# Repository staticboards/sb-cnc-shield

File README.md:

# This is the staticboards Arduino CNC shield for low-cost CNC machines.

This is a rework of the original arduino cnc shiled http://blog.protoneer.co.nz/arduino-cnc-shield/

## Why did you make a new Arduino CNC shield?

We were trying to make a new **low-cost** CNC machine for makers and hobbyist.

We found that it is not hard to design a simple aluminum structure with some 3d printed parts, using open software like FreeCAD.

But surprising, there are not many options for electronics part. And we didn’t find any open source shield for Arduino. Maybe we are wrong! But with a quick search, we didn't find anything.

We found one **Arduino CNC** shield that is being sold on eBay or Aliexpress. But the authors don’t like the idea of Chinese manufacturers making boards without any real collaboration (*something that I agree, open hardware is about community*). I couldnt find source files for this board.

So, as we decided that it is time to learn KiCad (a real open source software for PCB design), and we decided to make the PCB of this board, using the same pin layout, to get experience with KiCad.

And this is the final result: The **SB CNC Shield for Arduino Uno, 100% compatible with GRBL**.

We followed the same philosophy of our popular RAMPS 1.4 SB: Branded components, like the Molex connector, beautiful design with the black PCB and golden finish, and fully tested before shipping.

## What can you do with the SB CNC Shield?

The main idea behind this shield is that you can make your own functional CNC with a limited budget.

If you are interested in robots, you should make your own CNC machine. There are many problems that are not obvious at first. Motors, drivers, heat, software, belts, backslash.

Even if you want to buy an expensive machine, and you don't have any previous experience with CNC, it is a very good idea to make one by yourself.

**SB CNC SHIELD is 100% open hardware**. It is designed with *KiCad*, and you can read the schematics, check the PCB design, learn about electronics, improve it, whatever.

And the most important part with Open Hardware, we can create a community, share experiences, new ideas and fix problems.

This board is 100% compatible with the popular GRBL firmware. You don't need special configurations. Plug and Play. 

And there is a huge community behind this project, You can be part of it!

## Why no a full CNC board?

Well, you can go with a complete board. If you are serious about CNC, you should do it. A complete board is autonomous. You don't need a computer to send commands to the machine.

There are some boards open source, with a good community. That is very important if you want good support.
But most of them, they are closed source. Or they have a custom firmware.

For example, some integrated boards include the drivers within the board. That could be a problem. Drivers can get hot and it is not difficult to burn one. And in some cases, it is a good idea to use different drivers for each axis. 

And they have a higher price. Usually more than $100. If you are making a small CNC, for casual projects, this is a big deal.

## What else do I need?

To build a complete CNC machine you will need:

- One Arduino Uno
- At least, 3 drivers for the motors (you can use the popular A4988, or the more powerful DRV8825)
- One bipolar stepper motor for each axis
- One power supply. You can reuse your PC power supply with our ATX Board.
- The spindle (you can use a Dremel or buy a spindle on eBay) or a laser diode.
- The structure (aluminum t-slots, printed parts, etc)

## SB CNC Shield Features

- Beautiful design in Black. With Gold finish,  colored pin headers and a blue reset button.
- Cute easy yellow jumpers!
- 100% Compatible with the GRBL firmware. Plug and Play.
- You can duplicate any axis, or sacrifice your spindle control for a 4th axis. Simply change the jumpers, and duplicate any axis.
- Molex power connector rated at 15A. Cheap Chinese plastic connectors can get burned.
- You can use AWG22 cables for the power supply.
- 35V Capacitors. You can use 24V power supplies without any problem.-
- Endstops for X,Y,Z. You can connect the maximum and minimum limit for each axis.
- Easy to Access Reset button
- Configurable Emergency Button (normally open or normally closed)
- You can use the PWM features in GRBL to control the spindle speed. This is a great feature for metal and wood works.
- You can configure micro stepping for each driver, for a fluid movement.
- External driver connector. You can use professional and expensive drivers, like the Gecko drivers.
- You can use the extended pins from GRBL, like Coolant, Pause/Hold, Resume, and Abort
- UART connectors. You can use a Bluetooth adapter for a wireless CNC machine.
- i2c connection. You can use a temperature sensor for example (but you have to modify the GRBL source code)

## Useful Links

- http://blog.protoneer.co.nz/arduino-cnc-shield/ Original design. It has many guides and tutorials.
- https://github.com/grbl/grbl : GRBL firmware. You should learn how to use it
- https://github.com/winder/Universal-G-Code-Sender Graphical Interface, written in Java
- https://www.staticboards.com/ : Our website
- https://github.com/staticboards/sb-cnc-shield : github original repository

## License

**Creative-Commons 3.0 CC BY-SA**

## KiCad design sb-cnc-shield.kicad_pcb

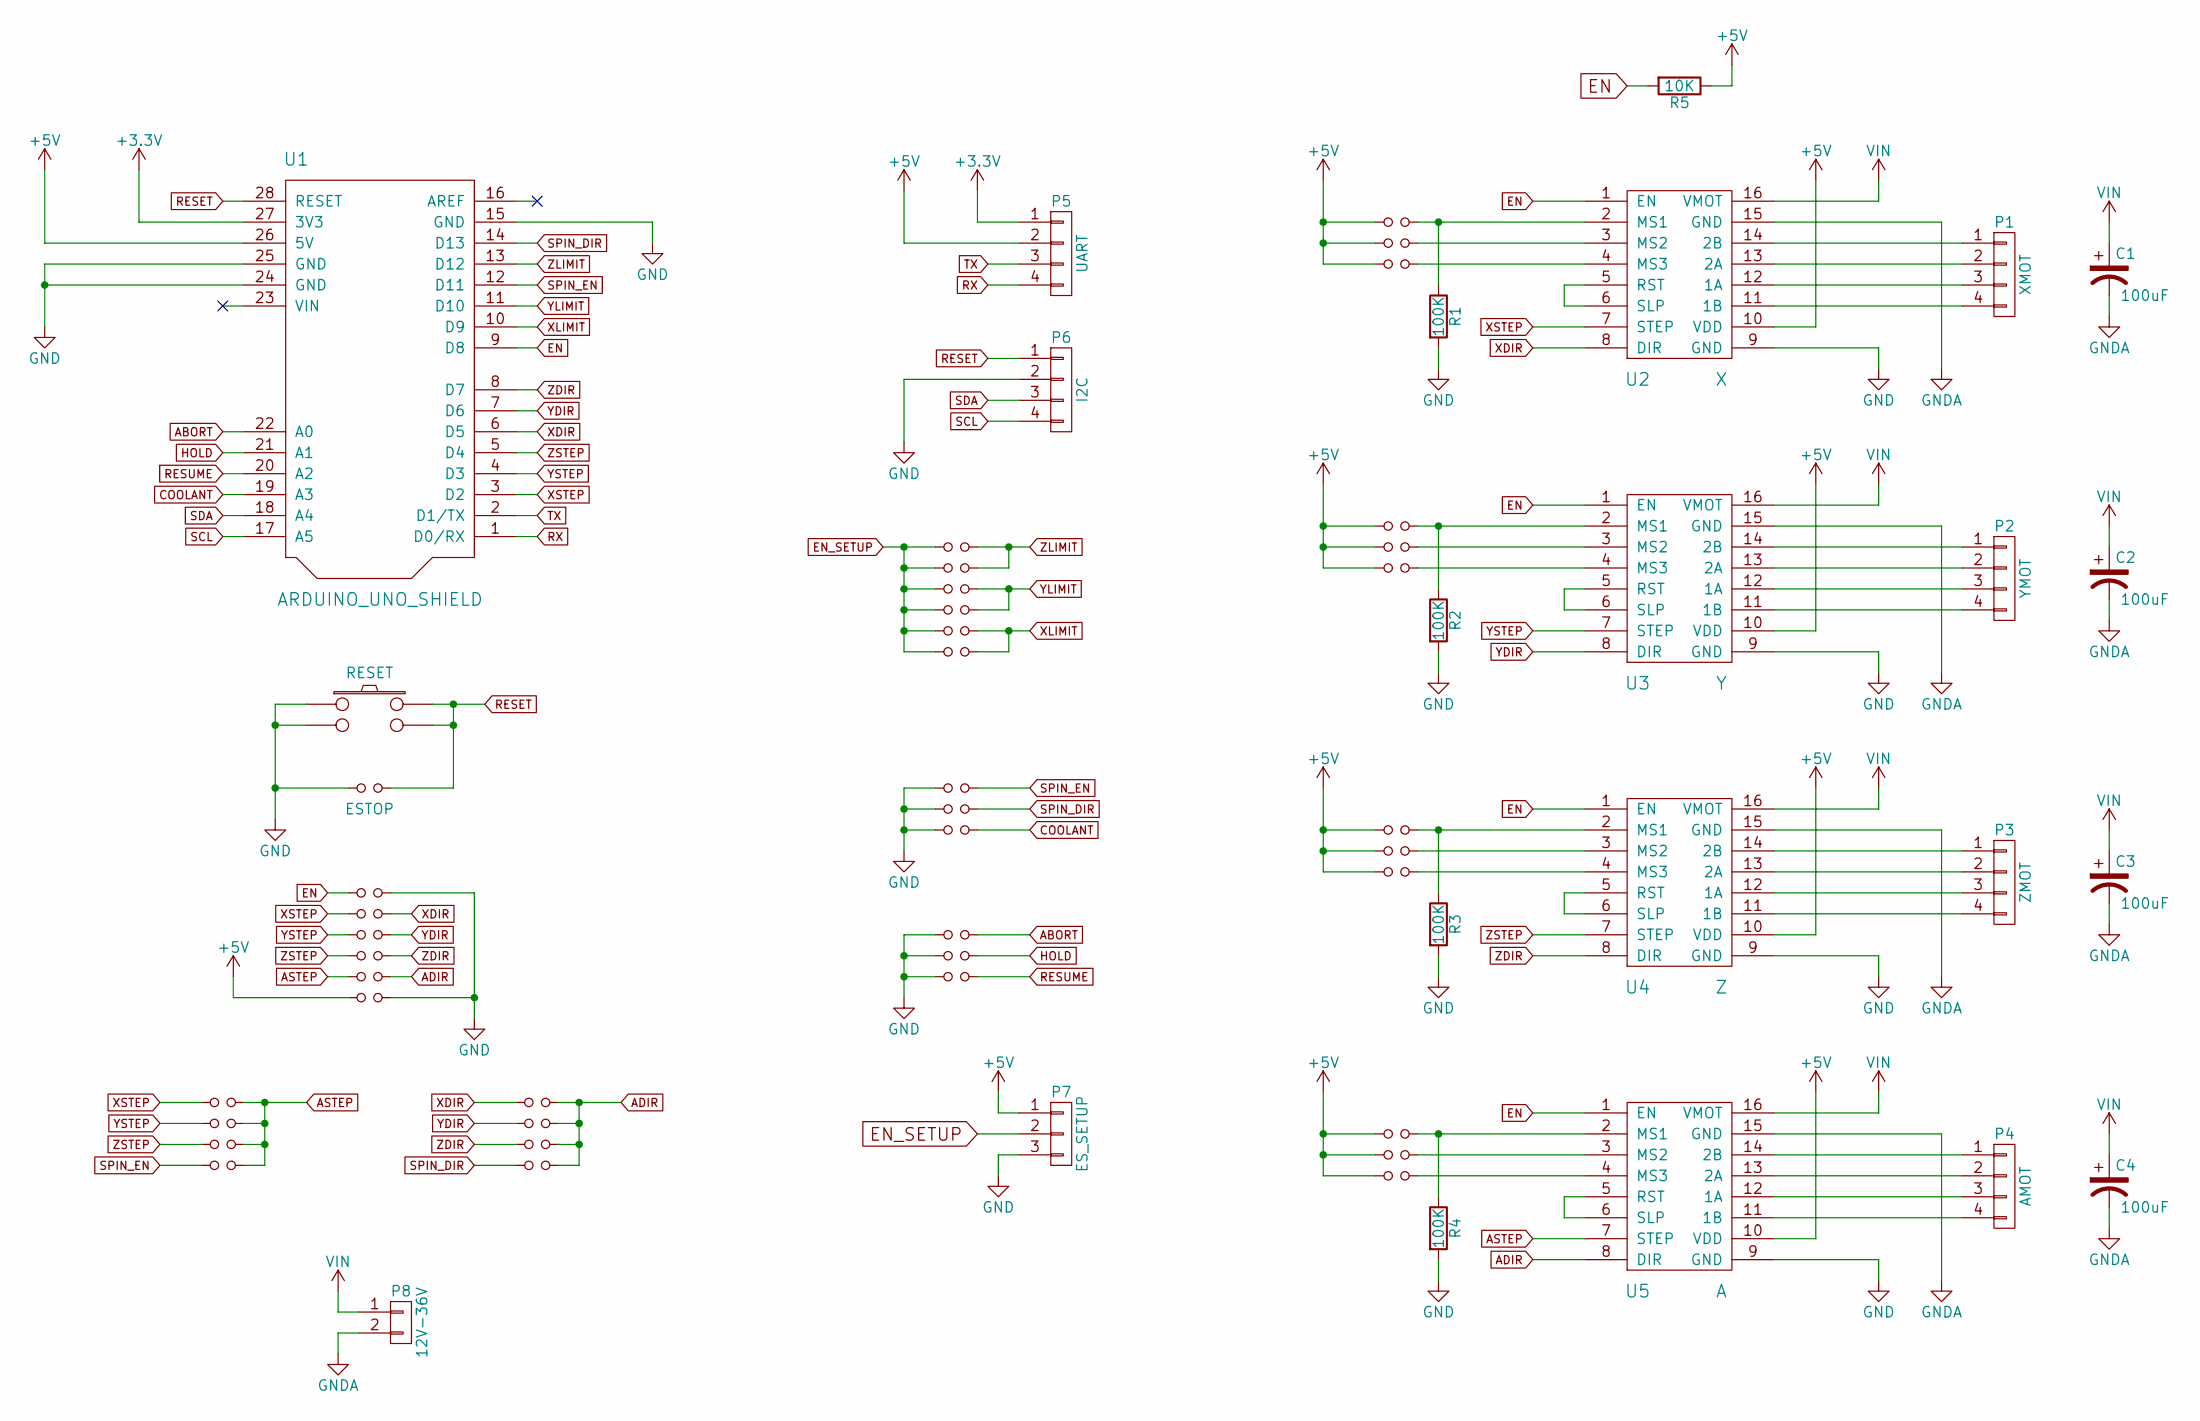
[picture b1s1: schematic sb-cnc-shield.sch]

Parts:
C1, C2, C3, C4: 100uF; c_elec_6.3x7.7
JP1, JP2, JP3, JP4, JP5, JP6, JP7, JP8, JP9, JP10, JP11, JP12, JP32, JP33, JP34, JP35, JP36, JP37, JP38, JP39: Jumper_NO_Small; Pin_100mil_Header_Straight_1x02
JP13: Z+; Pin_100mil_Header_Straight_1x02
JP14: Z-; Pin_100mil_Header_Straight_1x02
JP15: Y+; Pin_100mil_Header_Straight_1x02
JP16: Y-; Pin_100mil_Header_Straight_1x02
JP17: X+; Pin_100mil_Header_Straight_1x02
JP18: X-; Pin_100mil_Header_Straight_1x02
JP19: SpinEn; Pin_100mil_Header_Straight_1x02
JP20: SpinDir; Pin_100mil_Header_Straight_1x02
JP21: CoolEn; Pin_100mil_Header_Straight_1x02
JP22: Abort; Pin_100mil_Header_Straight_1x02
JP23: Hold; Pin_100mil_Header_Straight_1x02
JP24: Resume; Pin_100mil_Header_Straight_1x02
JP25: ESTOP; Pin_100mil_Header_Straight_1x02
JP26: EN/GND; Pin_100mil_Header_Straight_1x02
JP27: XSTEP/DIR; Pin_100mil_Header_Straight_1x02
JP28: YSTEP/DIR; Pin_100mil_Header_Straight_1x02
JP29: ZSTEP/DIR; Pin_100mil_Header_Straight_1x02
JP30: ASTEP/DIR; Pin_100mil_Header_Straight_1x02
JP31: +5V/GND; Pin_100mil_Header_Straight_1x02
P1: XMOT; Pin_Header_Straight_2x04
P2: YMOT; Pin_Header_Straight_2x04
P3: ZMOT; Pin_Header_Straight_2x04
P4: AMOT; Pin_Header_Straight_2x04
P5: UART; Pin_Header_Straight_1x04
P6: I2C; Pin_Header_Straight_1x04
P7: ES_SETUP; Pin_Header_Straight_1x03
P8: 12V-36V; CONN_01x02_PITCH_5.08mm
R1, R2, R3, R4: 100K; R_0805
R5: 10K; R_0805
SW1: RESET; SWITCH_TACTILE_6.5_PTH
U1: ARDUINO_UNO_SHIELD; ARDUINO_SHIELD
U2: X; POLOLU_STEPPER_DRIVER
U3: Y; POLOLU_STEPPER_DRIVER
U4: Z; POLOLU_STEPPER_DRIVER
U5: A; POLOLU_STEPPER_DRIVER

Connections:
+3V3: P5.1, U1.27 (3V3)
+5V: JP1.1, JP2.1, JP3.1, JP4.1, JP5.1, JP6.1, JP7.1, JP8.1, JP9.1, JP10.1, JP11.1, JP12.1, JP31.1, P5.2, P7.1, R5.1, U1.26 (5V), U2.10 (VDD), U3.10 (VDD), U4.10 (VDD), U5.10 (VDD)
ABORT: JP22.2, U1.22 (A0)
ADIR: JP30.2, JP36.2, JP37.2, JP38.2, JP39.2, U5.8 (DIR)
ASTEP: JP30.1, JP32.2, JP33.2, JP34.2, JP35.2, U5.7 (STEP)
COOLANT: JP21.2, U1.19 (A3)
EN: JP26.1, R5.2, U1.9 (D8), U2.1 (EN), U3.1 (EN), U4.1 (EN), U5.1 (EN)
EN_SETUP: JP13.1, JP14.1, JP15.1, JP16.1, JP17.1, JP18.1, P7.2
GND: JP19.1, JP20.1, JP21.1, JP22.1, JP23.1, JP24.1, JP25.1, JP26.2, JP31.2, P6.2, P7.3, R1.2, R2.2, R3.2, R4.2, SW1.1, SW1.2, U1.15 (GND), U1.24 (GND), U1.25 (GND), U2.9 (GND), U3.9 (GND), U4.9 (GND), U5.9 (GND)
GNDA: C1.2, C2.2, C3.2, C4.2, P8.2, U2.15 (GND), U3.15 (GND), U4.15 (GND), U5.15 (GND)
HOLD: JP23.2, U1.21 (A1)
unnamed: JP1.2, R1.1, U2.2 (MS1)
unnamed: JP2.2, U2.3 (MS2)
unnamed: JP3.2, U2.4 (MS3)
unnamed: JP4.2, R2.1, U3.2 (MS1)
unnamed: JP5.2, U3.3 (MS2)
unnamed: JP6.2, U3.4 (MS3)
unnamed: JP7.2, R3.1, U4.2 (MS1)
unnamed: JP8.2, U4.3 (MS2)
unnamed: JP9.2, U4.4 (MS3)
unnamed: JP10.2, R4.1, U5.2 (MS1)
unnamed: JP11.2, U5.3 (MS2)
unnamed: JP12.2, U5.4 (MS3)
unnamed: P1.1, U2.14 (2B)
unnamed: P1.2, U2.13 (2A)
unnamed: P1.3, U2.12 (1A)
unnamed: P1.4, U2.11 (1B)
unnamed: P2.1, U3.14 (2B)
unnamed: P2.2, U3.13 (2A)
unnamed: P2.3, U3.12 (1A)
unnamed: P2.4, U3.11 (1B)
unnamed: P3.1, U4.14 (2B)
unnamed: P3.2, U4.13 (2A)
unnamed: P3.3, U4.12 (1A)
unnamed: P3.4, U4.11 (1B)
unnamed: P4.1, U5.14 (2B)
unnamed: P4.2, U5.13 (2A)
unnamed: P4.3, U5.12 (1A)
unnamed: P4.4, U5.11 (1B)
unnamed: U2.5 (RST), U2.6 (SLP)
unnamed: U3.5 (RST), U3.6 (SLP)
unnamed: U4.5 (RST), U4.6 (SLP)
unnamed: U5.5 (RST), U5.6 (SLP)
RESET: JP25.2, P6.1, SW1.3, SW1.4, U1.28 (RESET)
RESUME: JP24.2, U1.20 (A2)
RX: P5.4, U1.1 (D0/RX)
SCL: P6.4, U1.17 (A5)
SDA: P6.3, U1.18 (A4)
SPIN_DIR: JP20.2, JP39.1, U1.14 (D13)
SPIN_EN: JP19.2, JP35.1, U1.12 (D11)
TX: P5.3, U1.2 (D1/TX)
VIN: C1.1, C2.1, C3.1, C4.1, P8.1, U2.16 (VMOT), U3.16 (VMOT), U4.16 (VMOT), U5.16 (VMOT)
XDIR: JP27.2, JP36.1, U1.6 (D5), U2.8 (DIR)
XLIMIT: JP17.2, JP18.2, U1.10 (D9)
XSTEP: JP27.1, JP32.1, U1.3 (D2), U2.7 (STEP)
YDIR: JP28.2, JP37.1, U1.7 (D6), U3.8 (DIR)
YLIMIT: JP15.2, JP16.2, U1.11 (D10)
YSTEP: JP28.1, JP33.1, U1.4 (D3), U3.7 (STEP)
ZDIR: JP29.2, JP38.1, U1.8 (D7), U4.8 (DIR)
ZLIMIT: JP13.2, JP14.2, U1.13 (D12)
ZSTEP: JP29.1, JP34.1, U1.5 (D4), U4.7 (STEP)

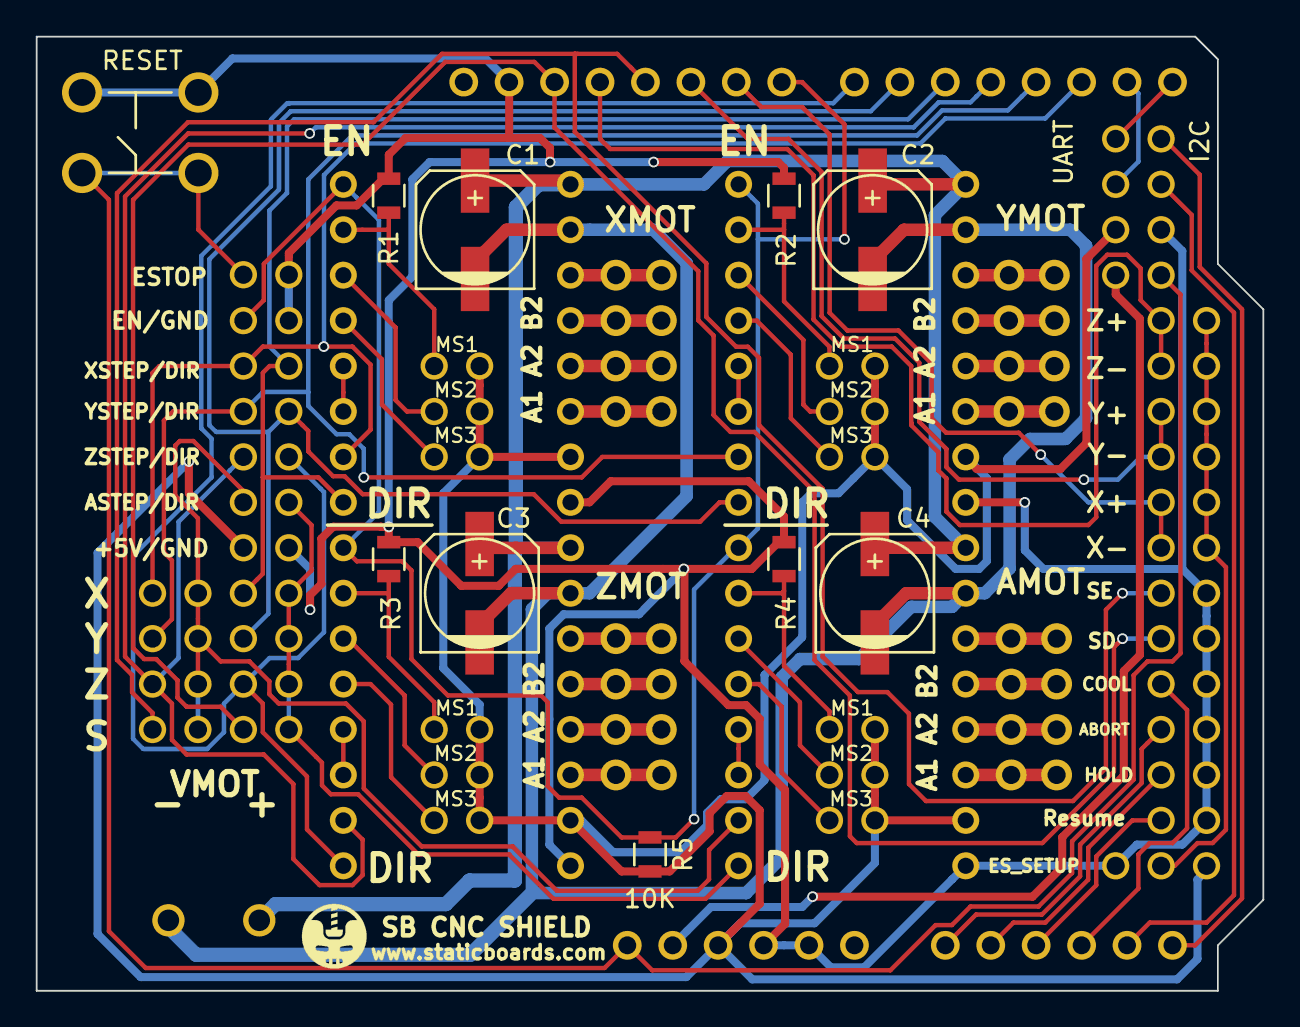
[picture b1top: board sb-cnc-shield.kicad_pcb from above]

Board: 2 copper layers, 68.6 x 53.3 mm, 62 parts (0 on the bottom side), 61 nets.

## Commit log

2016-06-08 First commit ever
2016-06-08 sb cnc shield
2016-06-14 captures
2016-06-14 license and readme
2016-06-14 renamed images
2016-06-14 testing images
2016-06-14 fine tuning the image list
2016-09-22 - changed width of tracks to motors, from 0.7 to 1.5 - add tracks to motors on down side
2018-12-13 upgraded to kicad 5
